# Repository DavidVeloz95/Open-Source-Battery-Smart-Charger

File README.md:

# Open Battery Smart Charger

Smart 2S Li-Ion battery charger designed in KiCad featuring input protection, power-path management, and intelligent charging control.

---

## Overview

This project implements an intelligent battery charging system for **2-cell Li-Ion batteries (8.4V)** with integrated protection and automatic power switching.

The system combines:

- Smart charging control
- Input overvoltage and overcurrent protection
- Automatic source/battery switching
- Auxiliary regulated 3.3V rail
- Battery monitoring interfaces

The design was developed in **KiCad 10** as part of a hardware/electronics engineering portfolio project.

---

## Features

- 2S Li-Ion battery charging (8.4V)
- Constant-current / constant-voltage (CC/CV) charging
- Input surge and fault protection
- Power-path management between external supply and battery
- Reverse current protection
- 3.3V regulated output for embedded systems
- Thermistor input for battery temperature supervision
- System and battery voltage interfaces

---

## System Architecture

### 1. Input Protection Stage

The input stage is protected using the **TPS26600** eFuse, providing:

- Overvoltage protection (OVP)
- Current limiting
- Fault protection
- Hot-plug robustness

This stage protects downstream electronics from abnormal supply conditions.

### 2. Smart Battery Charger

Battery charging is managed using the **LT3650**, configured for:

- 2S Li-Ion battery charging
- Constant-current / constant-voltage charging profile
- Battery temperature monitoring
- Charging status feedback

### 3. Power Path Management

The **LTC4412** controller enables automatic switching between:

- External DC power source
- Battery supply

This ensures uninterrupted system operation while preventing reverse current paths.

### 4. Auxiliary Power Rail

A dedicated **3.3V LDO regulator** powers low-voltage logic and embedded systems.

---

## Main Components

| Component | Function |
|---|---|
| LT3650 | Smart battery charger |
| TPS26600 | Input protection / eFuse |
| LTC4412 | Ideal diode power-path controller |
| LDK320AM33R | 3.3V voltage regulator |

---

## Specifications

| Parameter | Value |
|---|---|
| Battery Type | 2S Li-Ion |
| Charge Voltage | 8.4V |
| Charging Method | CC/CV |
| Logic Rail | 3.3V |
| Input Protection | OVP / current limiting |
| Design Tool | KiCad 10 |

---

## Repository Structure

```text
Open_Battery_Charger/
│
├── hardware/
│   ├── Open_Battery_Charger.kicad_pro
│   ├── Open_Battery_Charger.kicad_sch
│   ├── Open_Battery_Charger.kicad_pcb
│   └── fp-lib-table
│
├── docs/
│   ├── schematic.pdf
│   ├── schematic.png
│   ├── 2D_pcb_top.png
│   ├── 2D_pcb_bottom.png
│   ├── 3D_pcb_top.png
│   ├── 3D_pcb_bottom.png
│   ├── Detailed_Design_Procedure_LT3650.pdf
│   ├── Detailed_Design_Procedure_TPS2660
│   └── Open_Source_Battery_Smart_Charger_Specifications.pdf
│
└── production/
    ├── gerbers/
    └── bom.csv
```

---

## Schematic

---

## PCB Design

### Top View

### 3D Render

---

## Design Considerations

Key engineering decisions considered during development:

- Input fault protection for safer operation
- Efficient battery charging profile implementation
- Automatic power source switching
- Low-voltage regulation for embedded systems
- Modular architecture for maintainability

---

## Tools

- KiCad 10
- Datasheet-driven design methodology
- Electronic circuit validation

---

## Future Improvements

- PCB manufacturing and validation
- Thermal characterization
- Charging efficiency measurements
- Test reports and oscilloscope captures
- Firmware integration for battery monitoring

---

## License

This project is released under the MIT License.

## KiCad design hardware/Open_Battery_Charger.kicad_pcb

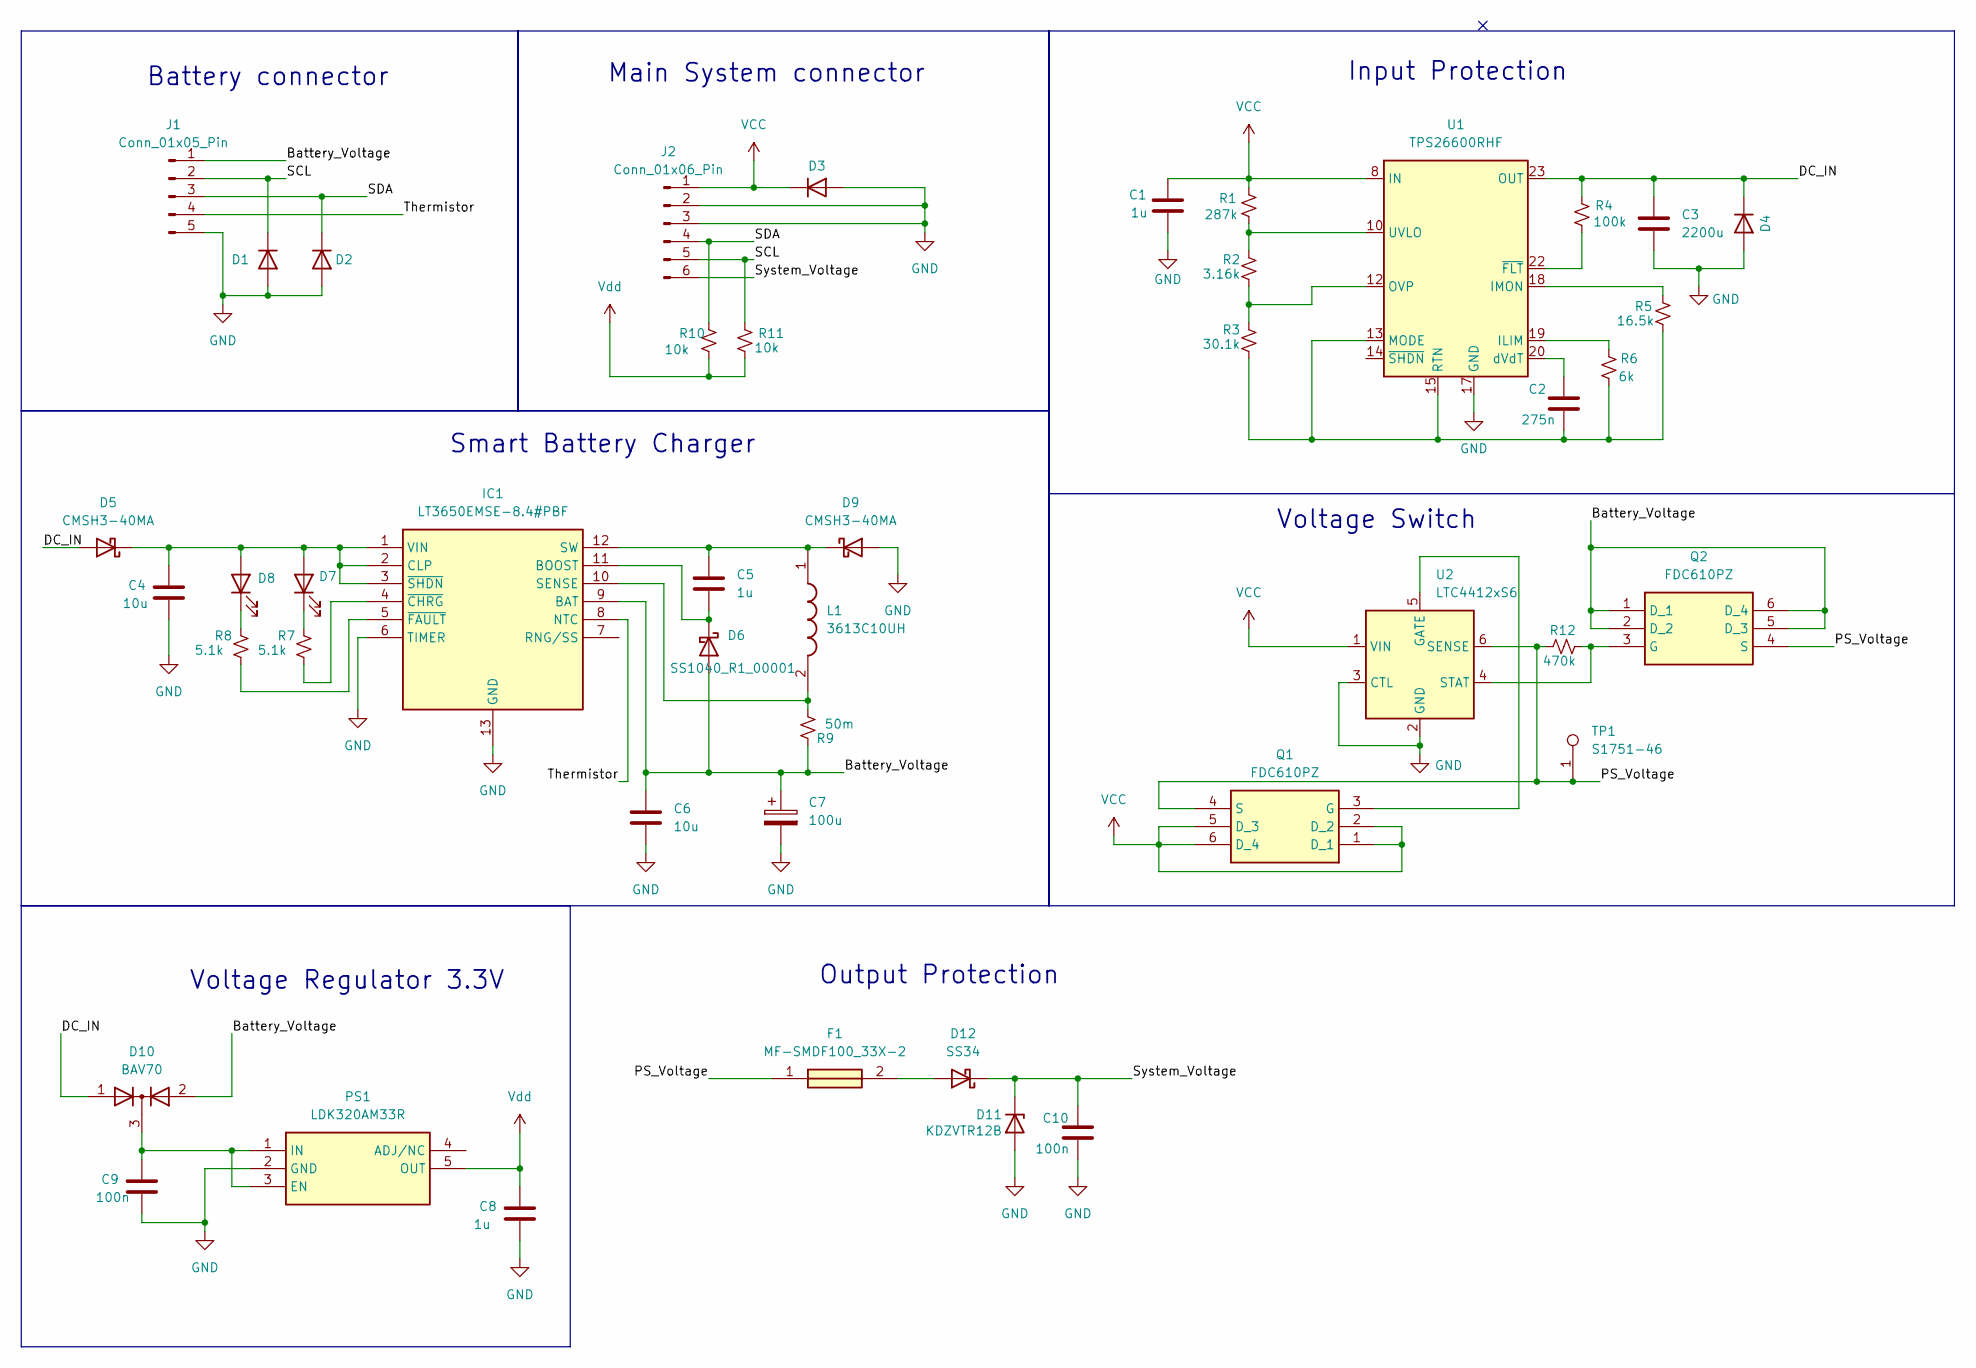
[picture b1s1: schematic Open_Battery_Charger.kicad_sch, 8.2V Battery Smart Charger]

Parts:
C1, C5, C8: 1u; C_0805_2012Metric_Pad1.18x1.45mm_HandSolder
C2: 275n; C_0805_2012Metric_Pad1.18x1.45mm_HandSolder
C3: 2200u; C_0805_2012Metric_Pad1.18x1.45mm_HandSolder
C4, C6: 10u; C_0805_2012Metric_Pad1.18x1.45mm_HandSolder
C7: 100u; CP_EIA-3528-21_Kemet-B_HandSolder
C9, C10: 100n; C_0805_2012Metric_Pad1.18x1.45mm_HandSolder
D1, D2, D3, D4: SMAJ12A-HP6AT/13; D_SMA
D5, D9: CMSH3-40MA; D_SMA
D6: SS1040_R1_00001; D_SOD-123
D7: Q62702P5179; LED_0805_2012Metric_Pad1.15x1.40mm_HandSolder
D8: Q62702P5178; LED_0805_2012Metric_Pad1.15x1.40mm_HandSolder
D10: BAV70; SOT-23
D11: KDZVTR12B; D_SOD-123
D12: SS34; D_SMA
F1: MF-SMDF100_33X-2; Mouser Part Number 652-MF-SMDF100/33X-2
IC1: LT3650EMSE-8.4#PBF; MSOP-12-1EP_3x4.039mm_P0.65mm_EP1.651x2.845mm_ThermalVias; Mouser Part Number 584-3650EMSE-8.4PBF
J1: Conn_01x05_Pin; PinHeader_1x05_P2.54mm_Vertical
J2: Conn_01x06_Pin; PinHeader_1x06_P2.54mm_Vertical
L1: 3613C10UH; C_1812_4532Metric_Pad1.57x3.40mm_HandSolder; Mouser Part Number 279-3613C10UH
PS1: LDK320AM33R; SOT-23-5_HandSoldering; Mouser Part Number 511-LDK320AM33R
Q1, Q2: FDC610PZ; SuperSOT-6; Mouser Part Number 512-FDC610PZ
R1: 287k; R_0805_2012Metric
R2: 3.16k; R_0805_2012Metric
R3: 30.1k; R_0805_2012Metric
R4: 100k; R_0805_2012Metric
R5: 16.5k; R_0805_2012Metric
R6: 6k; R_0805_2012Metric
R7, R8: 5.1k; R_0805_2012Metric
R9: 50m; R_0805_2012Metric
R10, R11: 10k; R_0805_2012Metric
R12: 470k; R_0805_2012Metric
TP1: S1751-46; TestPoint_Keystone_5015_Micro_Mini; Mouser Part Number 855-S1751-46
U1: TPS26600RHF; Texas_RHF0024A_VQFN-24-1EP_4x5mm_P0.5mm_EP2.65x3.65mm_Therm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
U2: LTC4412xS6; TSOT-23-6

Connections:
/Battery_Voltage: C6.1, C7.1, D6.2 (A), D10.2 (A), IC1.9 (BAT), J1.1, Q2.1 (D_1), Q2.2 (D_2), Q2.5 (D_3), Q2.6 (D_4), R9.1
/DC_IN: C3.1, D4.1 (K), D5.2 (A), D10.1 (A), R4.1, U1.23 (OUT), U1.24 (OUT)
/PS_Voltage: F1.1, Q1.4 (S), Q2.4 (S), R12.1, TP1.1, U2.6 (SENSE)
/SCL: D1.1 (K), J1.2, J2.5, R11.1
/SDA: D2.1 (K), J1.3, J2.4, R10.1
/System_Voltage: C10.1, D11.1 (K), D12.1 (K), J2.6
/Thermistor: IC1.8 (NTC), J1.4
GND: C1.1, C3.2, C4.2, C6.2, C7.2, C8.2, C9.2, C10.2, D1.2 (A), D2.2 (A), D3.2 (A), D4.2 (A), D9.2 (A), D11.2 (A), IC1.6 (TIMER), IC1.13 (GND), J1.5, J2.2, J2.3, PS1.2 (GND), U1.17 (GND), U2.2 (GND), U2.3 (CTL); also elsewhere on the board
unnamed: C4.1, D5.1 (K), D7.2 (A), D8.2 (A), IC1.1 (VIN), IC1.2 (CLP), IC1.3 (~SHDN)
unnamed: C5.2, D6.1 (K), IC1.11 (BOOST)
unnamed: D7.1 (K), R7.1
unnamed: D8.1 (K), R8.1
unnamed: C5.1, D9.1 (K), IC1.12 (SW), L1.1
unnamed: C9.1, D10.3 (K), PS1.1 (IN), PS1.3 (EN)
unnamed: D12.2 (A), F1.2
unnamed: IC1.10 (SENSE), L1.2, R9.2
unnamed: IC1.4 (~CHRG), R7.2
unnamed: IC1.5 (~FAULT), R8.2
unnamed: Q1.3 (G), U2.5 (GATE)
unnamed: Q2.3 (G), R12.2, U2.4 (STAT)
unnamed: R6.1, U1.19 (ILIM)
unnamed: R5.1, U1.18 (IMON)
unnamed: C2.2, R3.2, R5.2, R6.2, U1.13 (MODE), U1.15 (RTN), U1.25 (RTN)
unnamed: R2.2, R3.1, U1.12 (OVP)
unnamed: R1.2, R2.1, U1.10 (UVLO)
unnamed: C2.1, U1.20 (dVdT)
unnamed: R4.2, U1.22 (~FLT)
VCC: C1.2, D3.1 (K), J2.1, Q1.1 (D_1), Q1.2 (D_2), Q1.5 (D_3), Q1.6 (D_4), R1.1, U1.8 (IN), U1.9 (IN), U2.1 (VIN)
Vdd: C8.1, PS1.5 (OUT), R10.2, R11.2

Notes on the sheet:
Main System connector
Voltage Regulator 3.3V
Output Protection
Input Protection
Smart Battery Charger
Battery connector
Voltage Switch

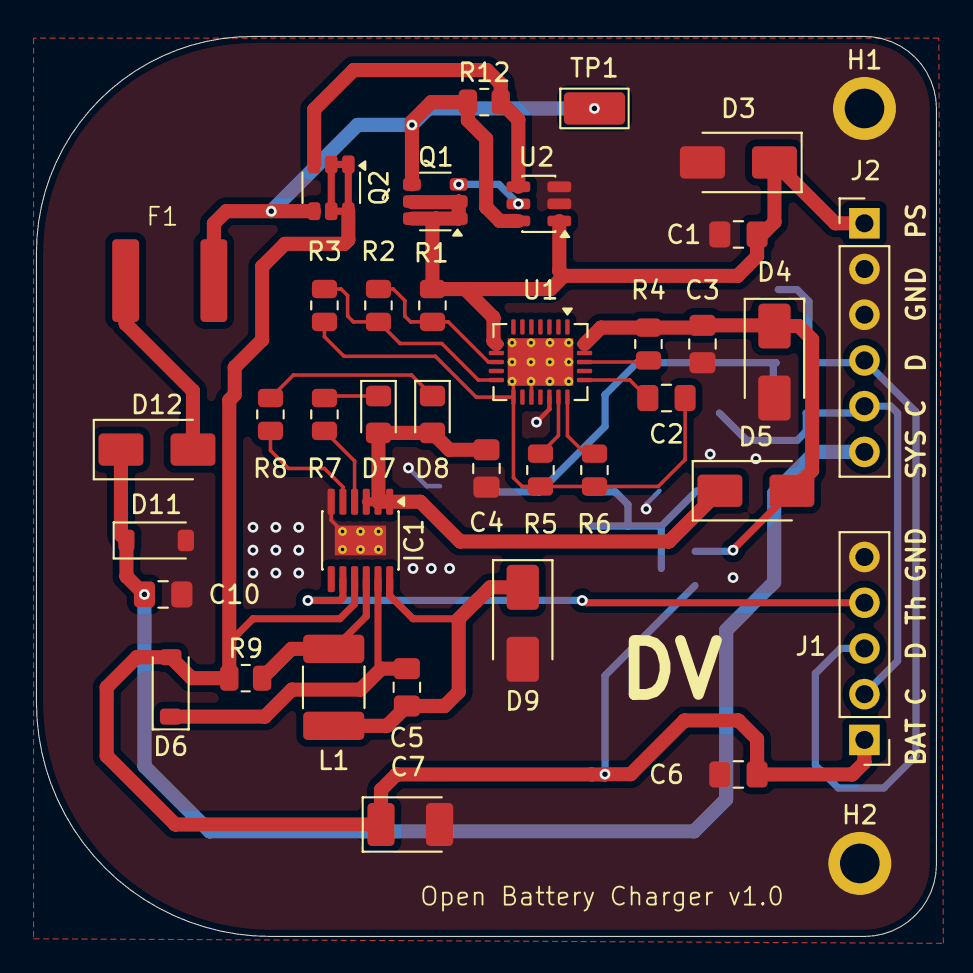
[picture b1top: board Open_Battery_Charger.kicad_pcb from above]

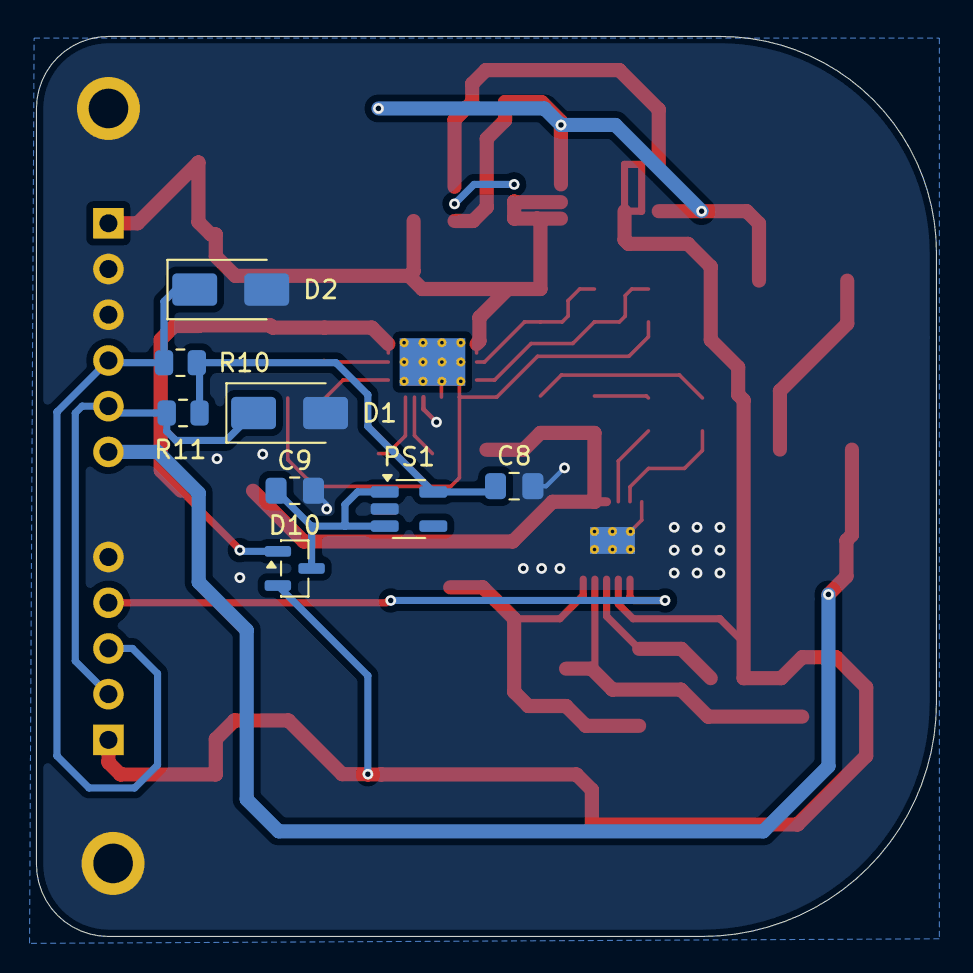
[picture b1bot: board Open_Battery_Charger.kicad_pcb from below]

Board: 2 copper layers, 50.0 x 50.0 mm, 47 parts (8 on the bottom side), 29 nets.

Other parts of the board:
H1, H2: MountingHole_2.2mm_M2_ISO7380_Pad

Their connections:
GND: H1.1, H2.2; also elsewhere on the board

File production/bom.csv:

Bill Of Materials (BOM),,,,,,,
#,Reference,Qty,Value,Descripción,Product Number,Manufacturer,Price
1,"C1,C5,C8",3,1u,Unpolarized capacitor,,,
2,C2,1,275n,Unpolarized capacitor,,,
3,C3,1,2200u,Unpolarized capacitor,,,
4,"C4,C6",2,10u,Unpolarized capacitor,,,
5,C7,1,100u,TLJP107M004R2700,,,
6,"C9,C10",2,100n,Unpolarized capacitor,,,
7,"D1,D2,D3,D4",4,SMAJ12A-HP6AT/13,ESD Protection Diodes / SMAJ DO214AC TVS Diodes 12V–19.9V AEC-Q101,SMAJ12A-HP6AT/13,YAGEO,"0,396"
8,"D5,D9",2,CMSH3-40MA,Schottky diode,,,
9,D6,1,SS1040_R1_00001,Schottky diode,,,
10,D7,1,Q62702P5179,Light emitting diode,,,
11,D8,1,Q62702P5178,Light emitting diode,,,
12,D10,1,BAV70,"Dual 100V 215mA high-speed switching diodes, common cathode, SOT-23",,,
13,D11,1,KDZVTR12B,Zener diode,,,
14,D12,1,SS34,"40V 3A Schottky Diode, SMA",,,
15,F1,1,MF-SMDF100_33X-2,Resettable Fuses - PPTC PTC RESETTABLE 1.1A 33V SMD 2018,,,
16,IC1,1,LT3650EMSE-8.4#PBF,Battery Management High Voltage 2 Amp Monolithic 2-Cell Li-Ion Battery Charger,,,
17,J1,1,Conn_01x05_Pin,"Generic connector, single row, 01x05, script generated",,,
18,J2,1,Conn_01x06_Pin,"Generic connector, single row, 01x06, script generated",,,
19,L1,1,3613C10UH,Fixed Inductors 250 mAmps +/- 10% 10 uH,,,
20,PS1,1,LDK320AM33R,LDO Voltage Regulators 200 mA low quiescent current and high PSRR voltage regulator,,,
21,"Q1,Q2",2,FDC610PZ,"Max rDS(on) = 75m at VGS = -4.5V, ID = -3.7A; Low gate charge (17nC typical).; High performance trench technology for extremely low rDS(on). ; SuperSOT-6 package: small footprint (72% smaller than standard SO-8) low profile (1mm thick).; Max rDS(on) = 42m at VGS = -10V, ID = -4.9A; RoHS compliant",,,
22,R1,1,287k,"Resistor, small US symbol",,,
23,R2,1,3.16k,"Resistor, small US symbol",,,
24,R3,1,30.1k,"Resistor, small US symbol",,,
25,R4,1,100k,"Resistor, small US symbol",,,
26,R5,1,16.5k,"Resistor, small US symbol",,,
27,R6,1,6k,"Resistor, small US symbol",,,
28,"R7,R8",2,5.1k,"Resistor, small US symbol",,,
29,R9,1,50m,"Resistor, small US symbol",,,
30,"R10,R11",2,10k,"Resistor, small US symbol,Thick Film Resistors - SMD General Purpose Chip Resistor 0805, 10kOhms, 5%, 1/8W",RC0805JR-7W10KL,YAGEO,"0,086"
31,R12,1,470k,"Resistor, small US symbol",,,
32,TP1,1,S1751-46,Hardware: SMT Test Point 1.63x3.25mm 2mm high,,,
33,U1,1,TPS26600RHF,"60V, 2A Current Limiting, Industrial eFuse, Reverse Current Blocking, Adjustable Overvoltage cut-off, Active Current Limiting, Circuit Breaker with auto-retry, VQFN-24",,,
34,U2,1,LTC4412xS6,"Low Loss PowerPath Controller, TSOT-23-6",,,

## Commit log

2026-05-22 Project upload
2026-05-22 schematic.png added
2026-05-25 Project update 25.05.2026
    hi
2026-05-25 New update 25.05.2026
